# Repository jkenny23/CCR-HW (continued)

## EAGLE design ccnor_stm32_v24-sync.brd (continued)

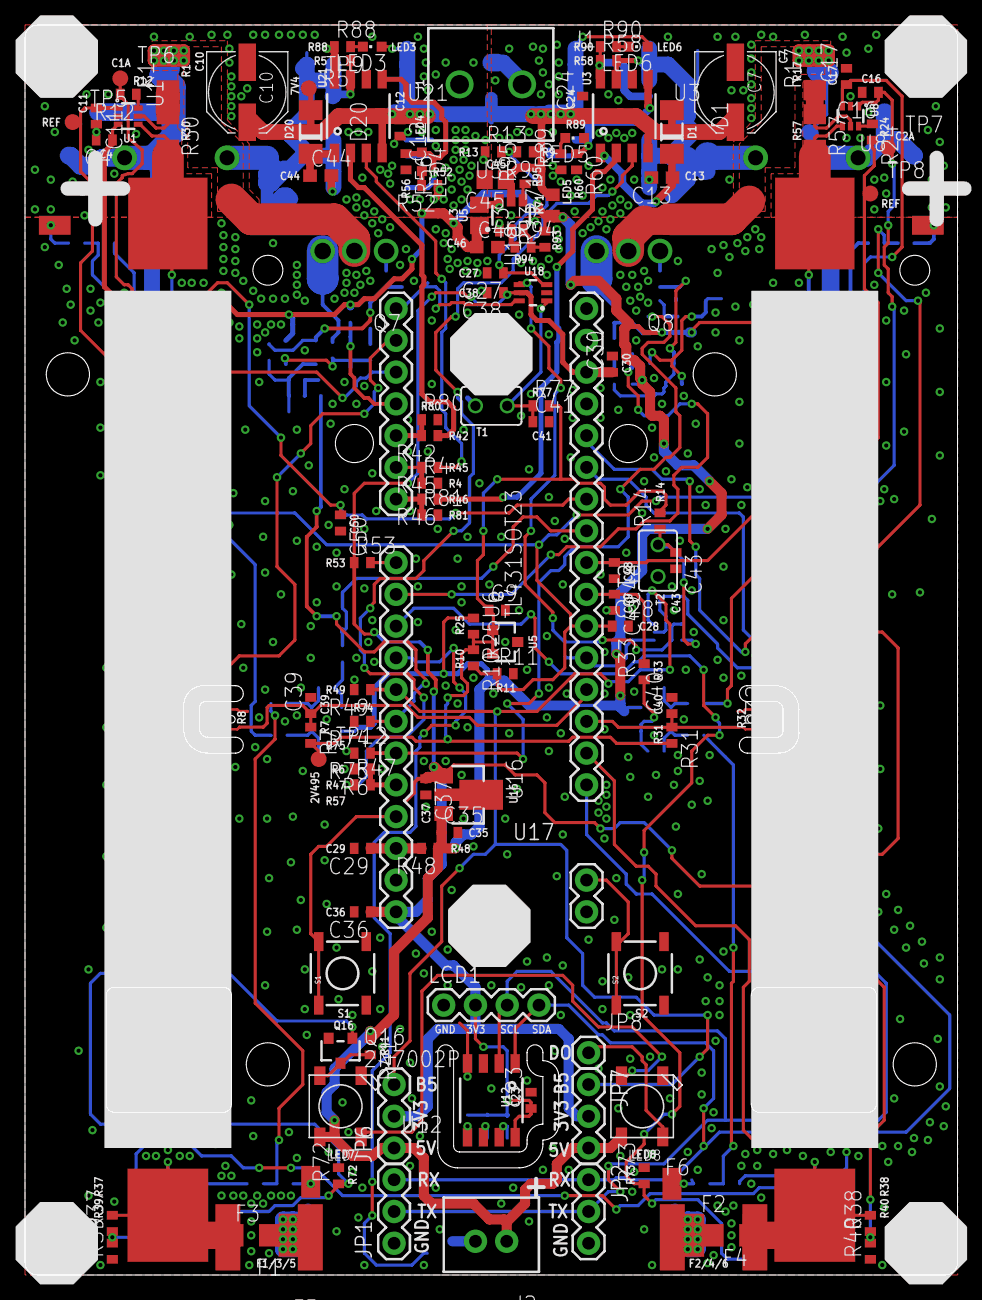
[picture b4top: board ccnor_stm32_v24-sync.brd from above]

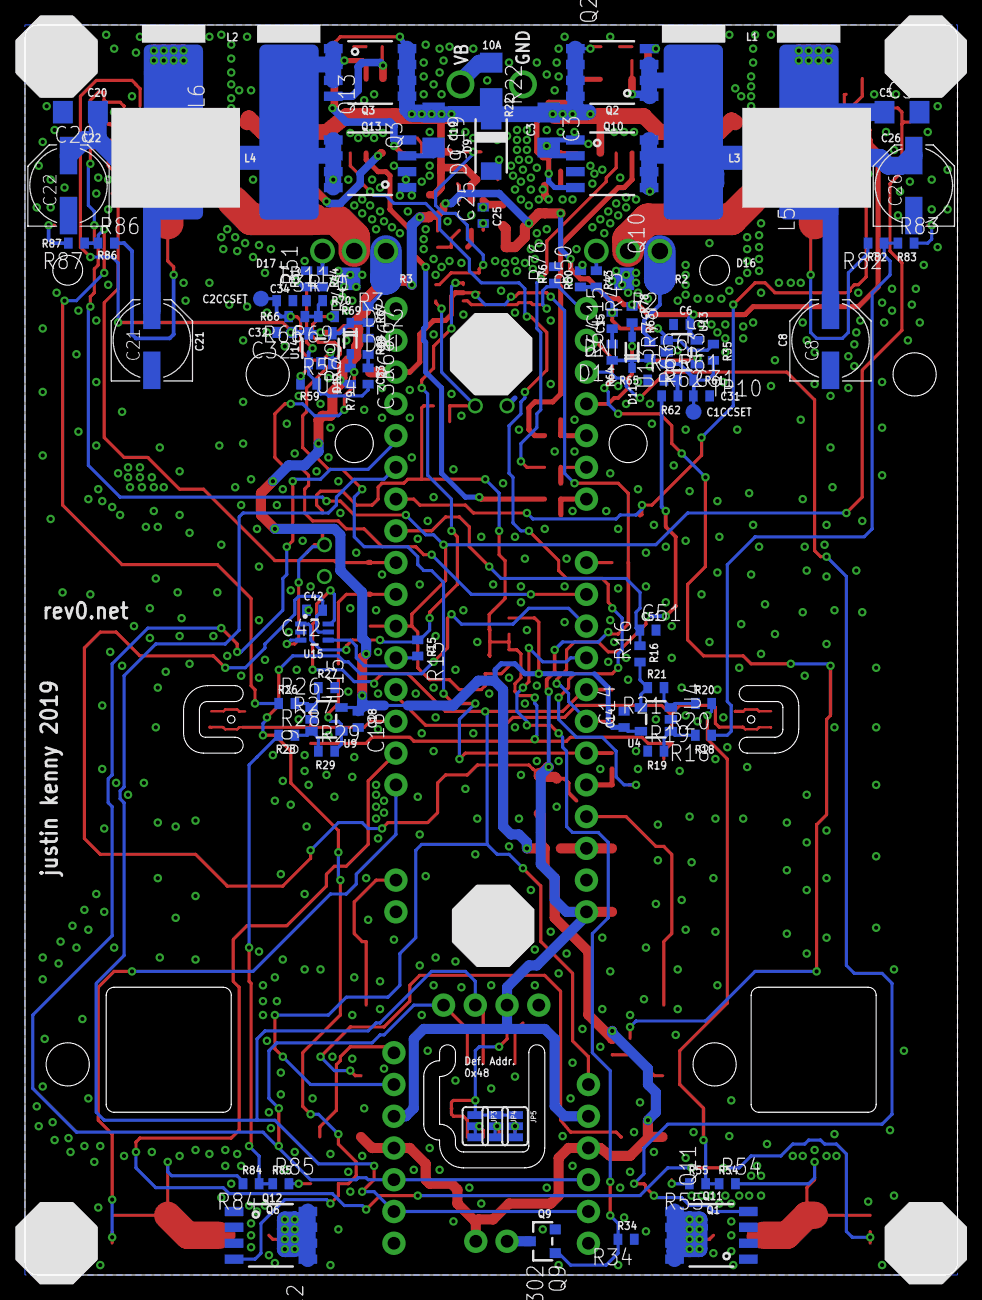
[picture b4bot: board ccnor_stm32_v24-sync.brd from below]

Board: 2 copper layers, 74.6 x 100.0 mm, 215 parts (84 on the bottom side), 107 nets.

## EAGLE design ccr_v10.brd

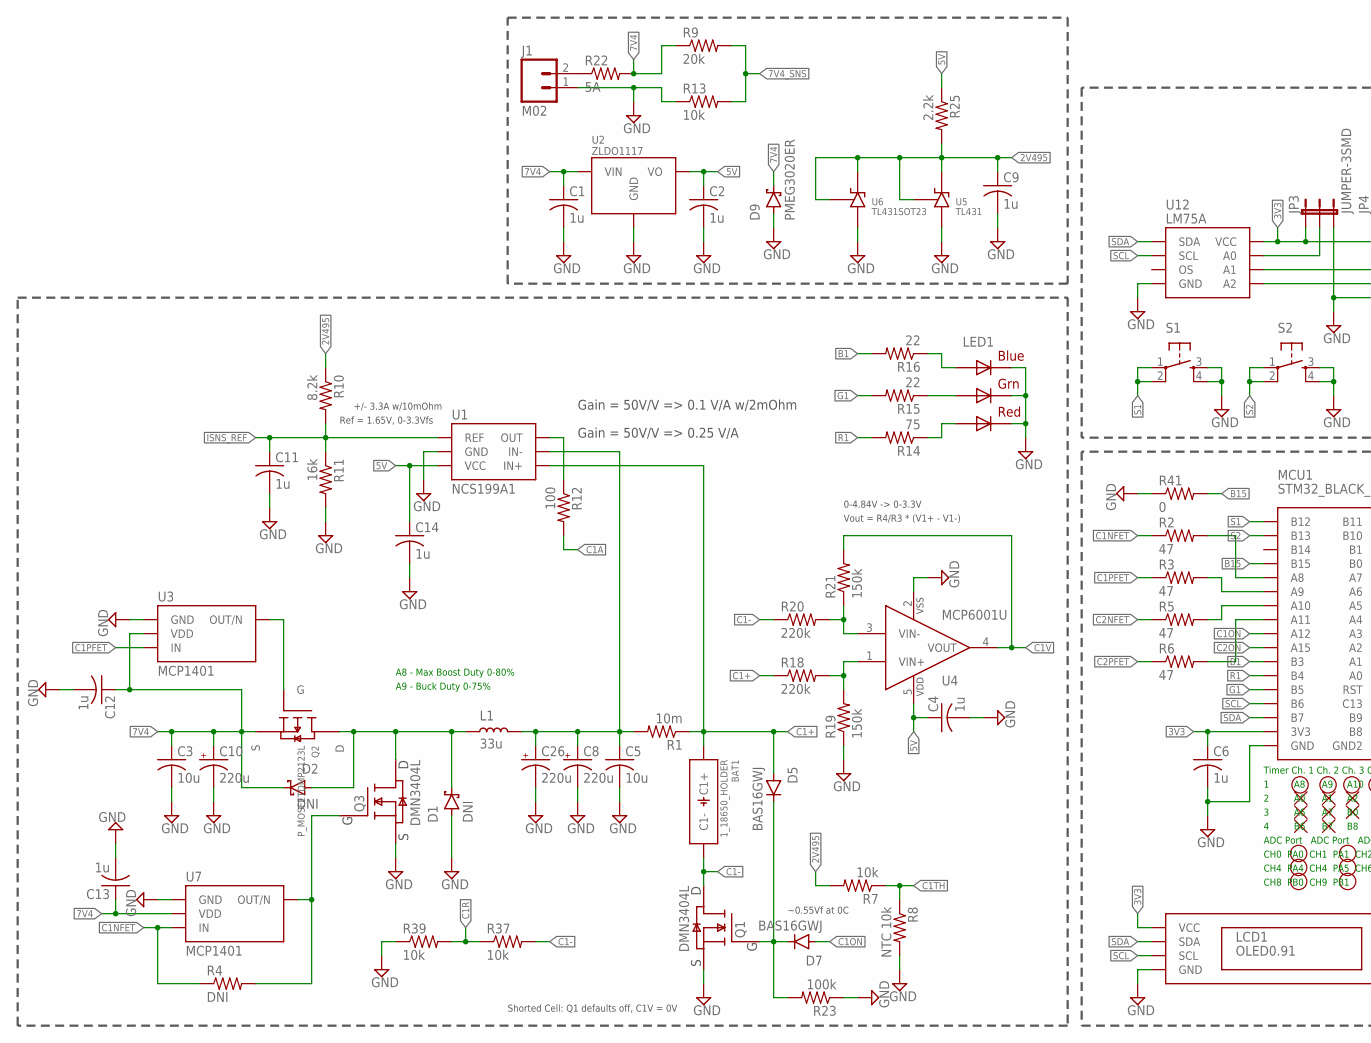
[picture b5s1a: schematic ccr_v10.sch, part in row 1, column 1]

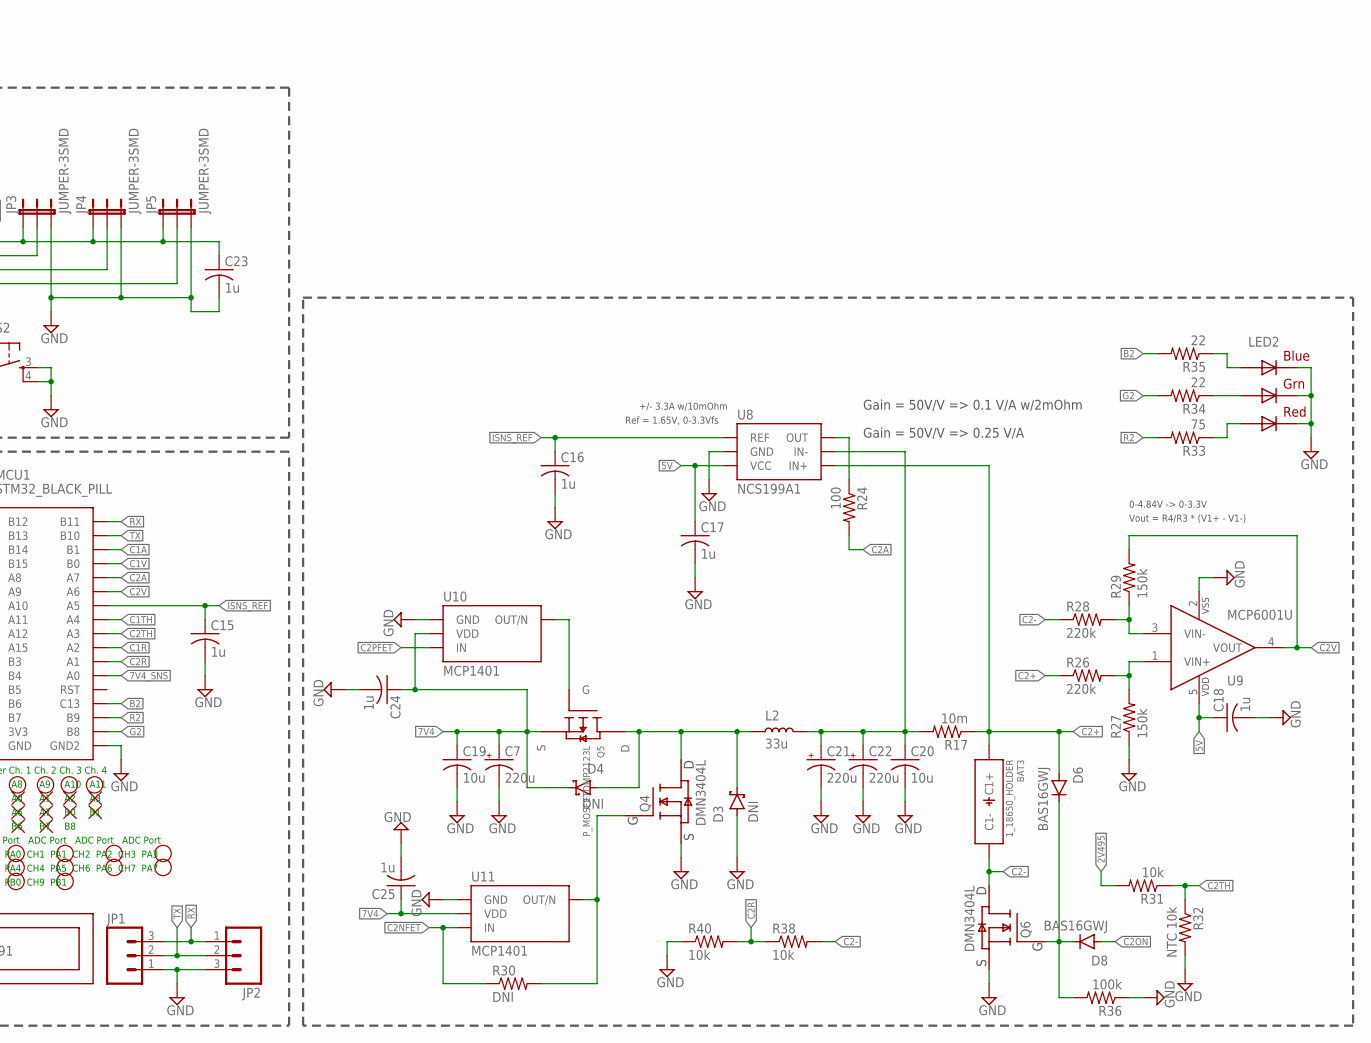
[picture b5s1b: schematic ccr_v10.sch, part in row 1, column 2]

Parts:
BAT1, BAT3: 1_18650_HOLDER; 1S_18650_SMD_NH
C1, C2, C4, C6, C9, C11, C12, C13, C14, C15, C16, C17, C18, C23, C24, C25: 1u; C0402
C3, C5, C19, C20: 10u; C1206
C7, C8, C10, C21, C22, C26: 220u; PANASONIC_D
D1, D2, D3, D4: DNI; SOD123W
D5, D6, D7, D8: BAS16GWJ; SOD323
D9: PMEG3020ER; SOD123W
J1: M02; PHOENIXCONTACT1935161
JP1, JP2: M03PTH; 1X03
JP3, JP4, JP5: JUMPER-3SMD; SJ_3
L1, L2: 33u; INDUCTOR_SMD_13MM
LCD1: OLED0.91
LED1, LED2: RGBLED5050
MCU1: STM32_BLACK_PILL; STM32_BLACK_PILL_BOT
Q1, Q3, Q4, Q6: DMN3404L; SOT23
Q2, Q5: P_MOSFETDMP2123L; SOT23
R1, R17: 10m; R2512
R2, R3, R5, R6: 47; R0402
R4, R30: DNI; R0402
R7, R13, R31, R37, R38, R39, R40: 10k; R0402
R8, R32: NTC 10k; R0402
R9: 20k; R0402
R10: 8.2k; R0402
R11: 16k; R0402
R12, R24: 100; R0402
R14, R33: 75; R0402
R15, R16, R34, R35: 22; R0402
R18, R20, R26, R28: 220k; R0402
R19, R21, R27, R29: 150k; R0402
R22: 5A; R1206
R23, R36: 100k; R0402
R25: 2.2k; R0402
R41: 0; R0402
S1, S2: TAC_SWITCHSMD; TACTILE_SWITCH_SMD
U1, U8: NCS199A1; SOT-363
U2: ZLDO1117; TO-261
U3, U7, U10, U11: MCP1401; SOT23-5
U4, U9: MCP6001U; SOT23-5
U5: TL431; SOT23-5
U6: TL431SOT23; SOT23
U12: LM75A; 8-SOIC

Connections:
2V495: C9.1, R7.2, R10.1, R25.2, R31.2, U5.3 (K), U5.4 (REF), U6.1 (K), U6.2 (REF)
3V3: C6.1, C23.1, JP3.1, JP4.1, JP5.1, LCD1.2-VCC (VCC), MCU1.3V3, U12.8 (VCC)
5V: C2.1, C4.1, C14.1, C17.1, C18.1, R25.1, U1.3 (VCC), U2.2 (VO), U2.4 (VO), U4.5 (VDD), U8.3 (VCC), U9.5 (VDD)
7V4: C1.1, C3.1, C7.+, C10.+, C12.1, C13.1, C19.1, C24.1, C25.1, D2.K (CATHODE), D4.K (CATHODE), D9.K (CATHODE), Q2.2 (S), Q5.2 (S), R9.1, R22.2, U2.3 (VIN), U3.2 (VDD), U7.2 (VDD), U10.2 (VDD), U11.2 (VDD)
7V4_SNS: MCU1.A0, R9.2, R13.2
B1: MCU1.B3, R16.2
B2: MCU1.C13, R35.2
B15: MCU1.B15, R41.2
C1+: BAT1.1+ (C1+), D5.A (ANODE), R1.1, R18.1, U1.4 (IN+)
C1-: BAT1.1- (C1-), Q1.3 (D), R20.1, R37.2
C1A: MCU1.B1, R12.2
C1NFET: R2.1, R4.1, U7.3 (IN)
C1ON: D7.A (ANODE), MCU1.A12
C1PFET: R3.1, U3.3 (IN)
C1R: MCU1.A2, R37.1, R39.2
C1TH: MCU1.A4, R7.1, R8.1
C1V: MCU1.B0, R21.2, U4.4 (VOUT)
C2+: BAT3.1+ (C1+), D6.A (ANODE), R17.1, R26.1, U8.4 (IN+)
C2-: BAT3.1- (C1-), Q6.3 (D), R28.1, R38.2
C2A: MCU1.A7, R24.2
C2NFET: R5.1, R30.1, U11.3 (IN)
C2ON: D8.A (ANODE), MCU1.A15
C2PFET: R6.1, U10.3 (IN)
C2R: MCU1.A1, R38.1, R40.2
C2TH: MCU1.A3, R31.1, R32.1
C2V: MCU1.A6, R29.2, U9.4 (VOUT)
G1: MCU1.B5, R15.2
G2: MCU1.B8, R34.2
GND: C1.2, C2.2, C3.2, C4.2, C5.2, C6.2, C7.-, C8.-, C9.2, C10.-, C11.2, C12.2, C13.2, C14.2, C15.2, C16.2, C17.2, C18.2, C19.2, C20.2, C21.-, C22.-, C23.2, C24.2, C25.2, C26.-, D1.A (ANODE), D3.A (ANODE), D9.A (ANODE), J1.1, JP1.1, JP2.3, JP3.3, JP4.3, JP5.3, LCD1.1=GND (GND), LED1.4 (BLUE_C), LED1.5 (RED_C), LED1.6 (GREEN_C), LED2.4 (BLUE_C), LED2.5 (RED_C), LED2.6 (GREEN_C), MCU1.GND1 (GND), MCU1.GND2, Q1.2 (S), Q3.2 (S), Q4.2 (S), Q6.2 (S), R8.2, R11.2, R13.1, R19.1, R23.1, R27.1, R32.2, R36.1, R39.1, R40.1, R41.1, S1.3, S1.4, S2.3, S2.4, U1.2 (GND), U2.1 (GND), U3.1 (GND), U3.4 (GND), U4.2 (VSS), U5.2 (A), U5.5 (A), U6.3 (A), U7.1 (GND), U7.4 (GND), U8.2 (GND), U9.2 (VSS), U10.1 (GND), U10.4 (GND), U11.1 (GND), U11.4 (GND), U12.4 (GND)
I1-: C5.1, C8.+, C26.+, L1.2, R1.2, U1.5 (IN-)
I1-1: C20.1, C21.+, C22.+, L2.2, R17.2, U8.5 (IN-)
IS1O: R12.1, U1.6 (OUT)
IS1O1: R24.1, U8.6 (OUT)
ISNS_REF: C11.1, C15.1, C16.1, MCU1.A5, R10.2, R11.1, U1.1 (REF), U8.1 (REF)
unnamed: MCU1.A8, R2.2
unnamed: MCU1.A9, R3.2
unnamed: R18.2, R19.2, U4.1 (VIN+)
unnamed: R20.2, R21.1, U4.3 (VIN-)
unnamed: Q2.1 (G), U3.5 (OUT/N)
unnamed: D1.K (CATHODE), D2.A (ANODE), L1.1, Q2.3 (D), Q3.3 (D)
unnamed: Q3.1 (G), R4.2, U7.5 (OUT/N)
unnamed: MCU1.A10, R5.2
unnamed: MCU1.A11, R6.2
unnamed: LED1.3 (BLUE_A), R16.1
unnamed: LED1.1 (GREEN_A), R15.1
unnamed: LED1.2 (RED_A), R14.1
unnamed: J1.2, R22.1
unnamed: D5.K (CATHODE), D7.K (CATHODE), Q1.1 (G), R23.2
unnamed: D6.K (CATHODE), D8.K (CATHODE), Q6.1 (G), R36.2
unnamed: R26.2, R27.2, U9.1 (VIN+)
unnamed: R28.2, R29.1, U9.3 (VIN-)
unnamed: D3.K (CATHODE), D4.A (ANODE), L2.1, Q4.3 (D), Q5.3 (D)
unnamed: Q5.1 (G), U10.5 (OUT/N)
unnamed: Q4.1 (G), R30.2, U11.5 (OUT/N)
unnamed: LED2.3 (BLUE_A), R35.1
unnamed: LED2.1 (GREEN_A), R34.1
unnamed: LED2.2 (RED_A), R33.1
unnamed: JP3.2, U12.7 (A0)
unnamed: JP4.2, U12.6 (A1)
unnamed: JP5.2, U12.5 (A2)
R1: MCU1.B4, R14.2
R2: MCU1.B9, R33.2
RX: JP1.3, JP2.1, MCU1.B11
S1: MCU1.B12, S1.1, S1.2
S2: MCU1.B13, S2.1, S2.2
SCL: LCD1.3=SCL (SCL), MCU1.B6, U12.2 (SCL)
SDA: LCD1.4-SDA (SDA), MCU1.B7, U12.1 (SDA)
TX: JP1.2, JP2.2, MCU1.B10

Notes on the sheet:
Gain = 50V/V => 0.25 V/A
Ref = 1.65V, 0-3.3Vfs
Gain = 50V/V => 0.1 V/A w/2mOhm
+/- 3.3A w/10mOhm
Vout = R4/R3 * (V1+ - V1-)
0-4.84V -> 0-3.3V
Timer Ch. 1 Ch. 2 Ch. 3 Ch. 4
1 A8 A9 A10 A11
2 A0 A1 A2 A3
3 A6 A7 B0 B1
4 B6 B7 B8
ADC Port ADC Port ADC Port ADC Port
CH0 PA0 CH1 PA1 CH2 PA2 CH3 PA3
CH4 PA4 CH4 PA5 CH6 PA6 CH7 PA7
CH8 PB0 CH9 PB1
Shorted Cell: Q1 defaults off, C1V = 0V
A8 - Max Boost Duty 0-80%
A9 - Buck Duty 0-75%
~0.55Vf at 0C

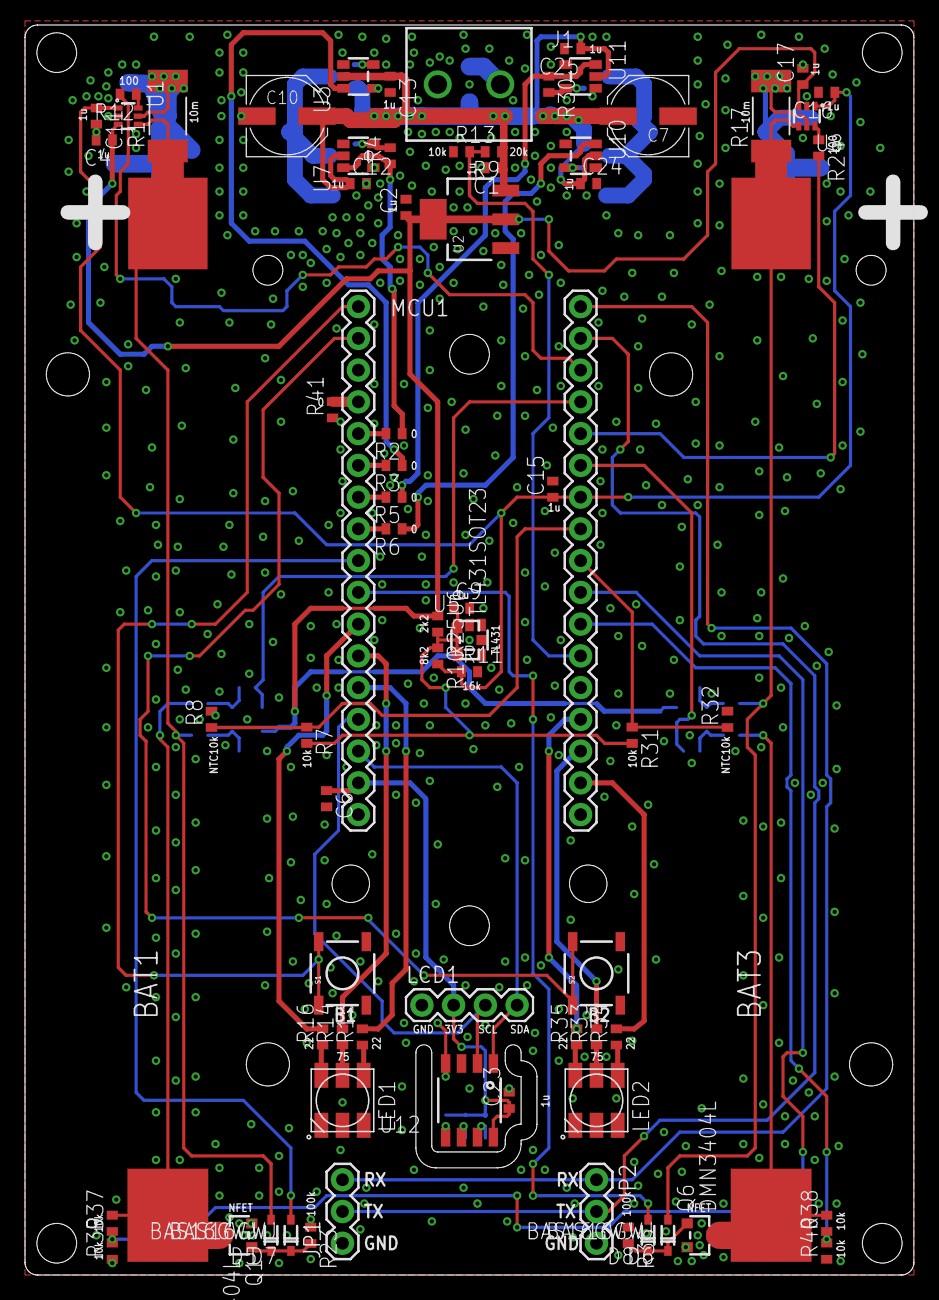
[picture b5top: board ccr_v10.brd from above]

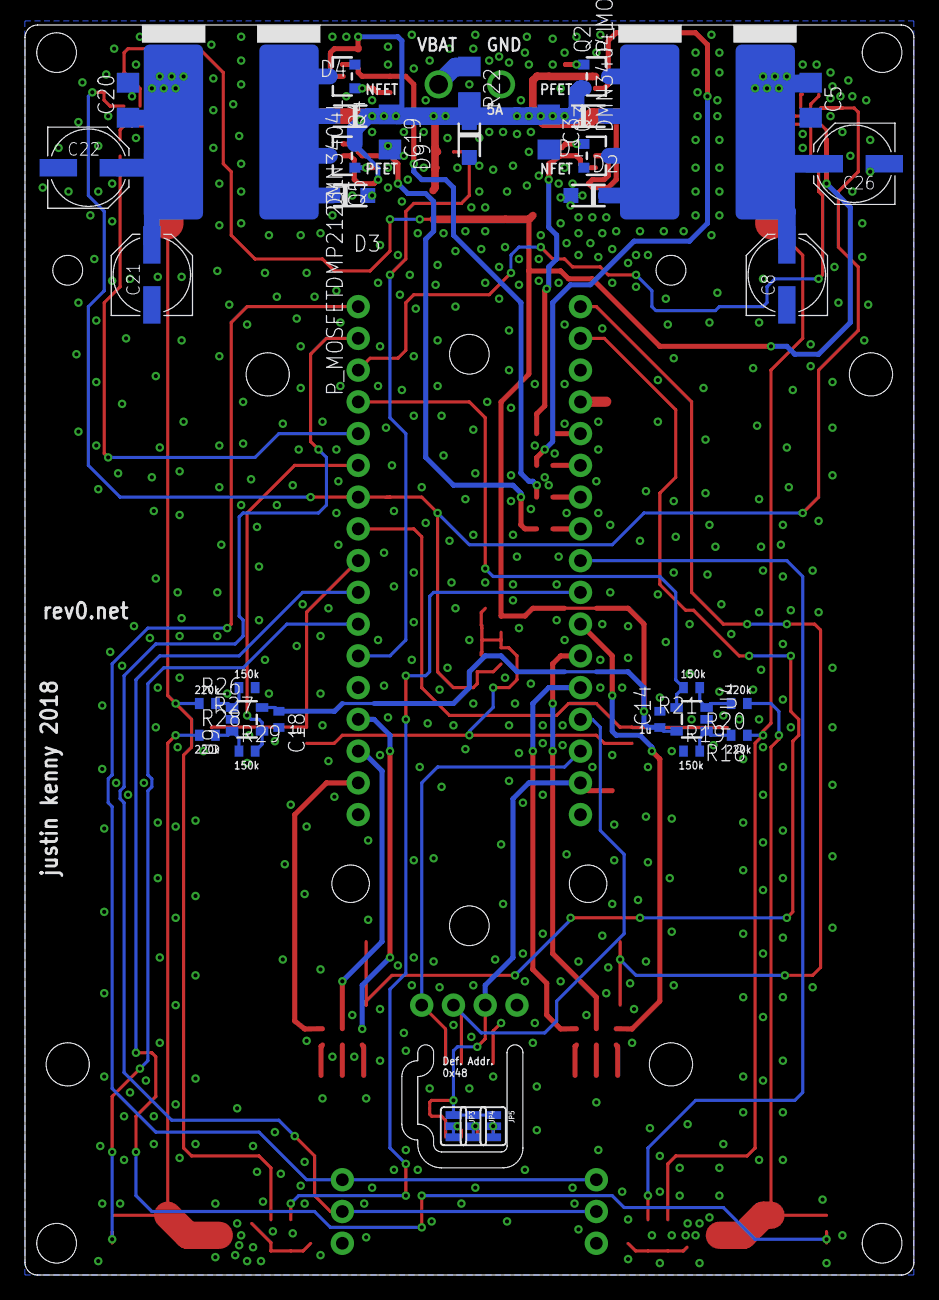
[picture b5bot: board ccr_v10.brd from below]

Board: 2 copper layers, 71.1 x 100.0 mm, 110 parts (35 on the bottom side), 68 nets.

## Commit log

2019-07-13 Minor fixes/changes for cleanup
    Minor fixes/changes for cleanup
2020-04-04 Moved 3 comps
2020-04-04 Added TL431 through-hole, fixed DRC errors
2020-04-04 Removed through-hole TL431, using C3113 basic part CJ431
2020-08-11 Updated U6 LCSC part number
    U6 TI SN74LVC1G3157DCKR, LCSC Part # C38663 is EOL in the parts library. Changed to equivalent Nexperia 74LVC1G3157GW, LCSC Part # C265126.
